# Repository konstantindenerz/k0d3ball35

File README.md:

# k0d3ball35

Read: **kodeball35**.

Designed and built by [Konstantin Denerz](https://konstantin-denerz.com) ·
[project page](https://konstantin-denerz.com/k0d3ball35/)

k0d3ball35 (kodeball35) is a wireless, low profile, 35-key split keyboard with an integrated 19 mm trackball.
Keyball-inspired column stagger and thumb arc, Kailh Choc V1 hot-swap switches, a nice!nano v2
on each half, ZMK firmware, two flat angular PCBs (18 keys left, 17 keys right) and the ball in a
case pocket right beside the thumb keys.

*Concept render, not a photo of a finished build.*

> ## ⚠️ Work in progress — do not build or order parts from this repository
>
> **k0d3ball35 is an unfinished design under active development. Nothing here has been
> manufactured, assembled or tested in hardware.**
>
> - No PCB in this repository has ever been fabricated, populated or electrically verified.
> - No case or cradle part has been printed and fit-checked against real switches, a real
>   trackball or a real battery.
> - Footprints, dimensions, the bill of materials and the firmware are all still changing, and
>   the geometry is revised between revisions without notice.
>
> **Do not send these gerbers to a fab, do not print these STLs, and do not buy components
> against this BOM.** If you do, you will very likely end up with parts that do not fit and
> money you cannot get back. Treat everything here as a design sketch to read, not a build
> guide to follow. Use at your own risk; there is no warranty of any kind.

## Status

| Subsystem | State | Where |
|-----------|-------|-------|
| Design specification | r2.4 (two PCBs, 35 keys, 19 mm ball pocket, battery bay under the controller on both halves) | [spec/01-design-spec.md](spec/01-design-spec.md) |
| Layout generator | r2.4 done, per-half outputs, exact coordinates in [spec/02-layout.md](spec/02-layout.md) | [hardware/layout](hardware/layout) |
| Left PCB (KiCad 10) | r2.4 routed, ERC and DRC clean, gerbers exported; battery bay on the back silkscreen | [hardware/left-pcb](hardware/left-pcb) |
| Right PCB (KiCad 10) | r2.4 routed, ERC and DRC clean, gerbers exported; battery bay on the back silkscreen | [hardware/right-pcb](hardware/right-pcb) |
| Trackball sensor | r2.4: bought PAW3222 module, no board of ours to fabricate; J1 re-ordered to the module's pinout | [spec/08-trackball-module.md](spec/08-trackball-module.md) |
| Trackball cradle | r2.4 pocket mount for 19.05 mm with the module tilted 65 degrees beside the ball, test print pending | [hardware/trackball-cradle](hardware/trackball-cradle) |
| Firmware (ZMK) | r2.4 in progress: 35 keys, one shared pin set | [firmware/zmk-config](firmware/zmk-config) |
| Documentation | build guide, firmware, fabrication, testing written for r2 | [docs](docs) |
| Case | printed tray, controller box cap, PCB guard, pocket cover and hinged lid per half (OpenSCAD); test print pending | [hardware/case](hardware/case), [spec/11-case.md](spec/11-case.md) |
| Tests and CI | pytest suite, workflows ready for GitHub | [tests](tests), [.github/workflows](.github/workflows) |

Open work is tracked as markdown tickets in [issues/](issues/README.md). The r2 change itself is
`hw-two-pcbs-r2`. Before the first PCB order, work through `hw-main-pcb-review-r1`,
`test-fab-gerber-viewer`, `hw-19mm-ball-sourcing` and a cradle test print (see
[spec/09-roadmap.md](spec/09-roadmap.md)).

## Features

- 35 keys: 3 rows x 5 columns per half plus 3 thumb keys on the left and 2 on the right (the ball
  takes the third position), 18 x 17 mm pitch
- Column stagger and thumb arc derived from the Keyball39 geometry, scaled to Choc spacing
- Kailh Choc V1 switches in hot-swap sockets (hot-swap only, like the Keyball)
- 19.05 mm (3/4 inch) POM trackball on the right half, resting on three 2 mm ceramic balls in a
  printed cradle that stands in a case pocket beside the PCB; bought PAW3222 sensor module tilted
  65 degrees beside the ball, connected with a 6-pin flat cable
- Low: keycaps 20.8 mm over the desk, ball top 23.75 mm, 27.3 mm with the transport lid on
- Fully wireless: nice!nano v2 (or SuperMini nRF52840) per half on 2.5 mm low-profile sockets,
  Bluetooth split, one LiPo cell per half (350 mAh LP552035 right, 150 mAh LP402025 left) in a bay under the PCB below the
  controller (the same bay on both halves), the controller's charger, JST-PH connector, slide
  power switch, reset button
- Two separate PCBs with identical controller wiring: no solder jumpers, no mirrored pin maps,
  no empty ball cutout on the left
- Angular outline: 90 degree steps along the column stagger, rectangular controller block, no rounding
- No LEDs, display or encoder on the PCB, to keep the height and the power draw down
- ZMK firmware on a pinned `main` revision with the PAW3222 driver, automatic mouse layer,
  scroll and snipe modes, ZMK Studio
- All geometry comes from one layout file; schematic, PCB, footprints and tests are generated from the same data

## Repository map

```
spec/                 specification, layout, BOM, build guide, firmware, fabrication, testing
docs/                 the published project page (tabs: exploded view, case, trackball, PCBs, keymap, BOM)
hardware/layout/      layout source (yaml), generated points, outline DXFs and previews per half
hardware/left-pcb/    KiCad project of the left PCB (18 keys), gerbers and renders
hardware/right-pcb/   KiCad project of the right PCB (17 keys, FPC connector, pocket notch)
hardware/lib/         project symbol and footprint libraries
hardware/trackball-cradle/  parametric cradle (pocket mount), STL and floor-footprint DXF exports
hardware/case/        parametric printed case per half (tray, cap, guard, lid), STLs and previews
firmware/zmk-config/  ZMK shield, keymap, build matrix
scripts/              generators and checks (schematic, routing, export, tickets)
tests/                pytest suite incl. KiCad ERC/DRC gates
issues/               markdown tickets and the generated index
```

## Documentation

| Document | Content |
|----------|---------|
| [00 Feasibility](spec/00-feasibility.md) | prior art, ball size research, risks, licensing, why this design |
| [01 Design specification](spec/01-design-spec.md) | requirements, pin map, matrix, FPC interface, geometry contract |
| [02 Layout](spec/02-layout.md) | key coordinates per half, stagger derivation, ball pocket |
| [03 Bill of materials](spec/03-bom.md) | parts, quantities per half, sources |
| [04 Build guide](spec/04-build-guide.md) | step by step assembly |
| [05 Firmware](spec/05-firmware.md) | flashing, pairing, tuning, battery |
| [06 Fabrication](spec/06-fabrication.md) | PCB order settings for both boards, gerber checklist |
| [07 Testing](spec/07-testing.md) | automated checks and bench procedure |
| [08 Trackball module](spec/08-trackball-module.md) | sensor module, cable, heights, pocket mount |
| [09 Roadmap](spec/09-roadmap.md) | verification before ordering, case, dongle, sensor variants |
| [10 Lessons from Keyball](spec/10-lessons-from-keyball.md) | holykeebs and Yowkees designs, known weaknesses and our response |
| [11 Printed case](spec/11-case.md) | tray, controller box cap, ball pocket, hinged lid as transport cover and tenting foot |
| [12 Order checklist](spec/12-order-checklist.md) | shop-by-shop parts list, what is ordered, JLCPCB and LCSC lines, printed parts, what waits for hardware |
| [Image prompts](spec/images/PROMPTS.md) | every picture as a generation prompt |

## Project page

The project page, [`docs/index.html`](docs/index.html), is published with GitHub Pages from
`docs/` on `main`. One tab per area: an overview, the interactive 3D exploded view of both halves
(explode slider, half switch, section through the ball, lid modes), the real printed parts of the
case and the trackball cradle, the three boards in 3D and as layer plots and the keymap. The page
shows the files; the markdown keeps the details, and the overview links to it.

The page is static; every file it loads carries a content hash (`?v=`, stamped by `make site`), so a visit never mixes cached files of two versions. It shows the real files: STLs and the KiCad GLBs are fetched from the
repository (raw.githubusercontent.com, branch `main`), nothing is copied into `docs/`. The data the
tabs need (layout, part facts, keymap, board facts) is generated into `docs/data/` by
`docs/build.py`: run `make site` after a change to the layout, the case, the boards, the keymap,
the BOM or the tickets; `tests/test_site.py` fails while the data is stale. `make site-serve`
serves the page with the files of the working tree at http://localhost:8000/docs/, which previews
a branch before it is merged.

## Quick start

```sh
brew install --cask kicad          # KiCad 10.0.7 (copy the app from the DMG if the cask asks for admin rights)
brew install openjdk               # Java for freerouting
brew install --cask openscad@snapshot   # OpenSCAD with the manifold backend, for the case and cradle
uv venv .venv && uv pip install --python .venv/bin/python -e ".[test]"
make freerouting-jar               # downloads freerouting 2.5.0 to build/
make test                          # full test suite
```

## Build the hardware files

Everything under `hardware/left-pcb/` and `hardware/right-pcb/` is generated; edit
`hardware/layout/k0d3ball35.yaml` and `scripts/k0d3/` instead of the KiCad files.

```sh
make layout                                   # points-*.json, outline-*.dxf, previews for both halves
JAVA=/opt/homebrew/opt/openjdk/bin/java \
FREEROUTING_JAR=build/freerouting.jar \
make sch pcb route gerbers                    # both halves: schematic + ERC, PCB, freerouting, DRC, export
scripts/build_board.sh right                  # one half: schematic + ERC, unrouted PCB, freerouting, DRC (retries until clean)
scripts/export.sh right                       # one half: gerbers, drill, zip, STEP, renders, schematic PDF, BOM, position file
make erc drc                                  # the KiCad gates on their own
make -C hardware/trackball-cradle             # cradle STLs, floor DXF, previews, stack.json
make case-data case                           # hardware/case: data.scad from the layout, tray/cap/lid STLs, previews, stack.json (needs OpenSCAD)
```

`HALVES=right make route` limits the looping targets to one half. `scripts/build_board.sh` expects
`kicad-cli` and KiCad's bundled Python at
`/Applications/KiCad/KiCad.app/Contents/MacOS/kicad-cli` and
`/Applications/KiCad/KiCad.app/Contents/Frameworks/Python.framework/Versions/Current/bin/python3`;
override with `KICAD_CLI=` and `KPY=`. Since r2.4 the two halves are the only KiCad projects in
the repository: the trackball sensor is a bought PAW3222 module, so there is nothing to generate
or fabricate for it.

Firmware is built by GitHub Actions from `firmware/zmk-config`; see
[spec/05-firmware.md](spec/05-firmware.md) for local builds and flashing.

```prompt
Top-down studio render of the right half of a low profile split keyboard, white background, soft
shadows. Bare black PCB with an angular, stepped outline, 17 Kailh Choc hot-swap sockets, small
SOD-123 diodes next to each key, two thumb key positions at the lower inner side and the ball
pocket where a third would be, a nice!nano
controller on low profile sockets in a rectangular block at the inner edge, a dashed rectangle
printed on the board under it marking the battery bay on the other face, an octagonal notch in the lower outer edge of the board where a beige
printed cradle holding a white 19 mm ball stands beside the PCB, a tiny flat flex cable running
from the cradle round the cup to a connector on the PCB. Clean, technical, product photography style.
```

## Credits

- [Keyball](https://github.com/Yowkees/keyball) by Yowkees: the column stagger, thumb arc and the
  idea of a trackball at the thumb are the design inspiration. No Keyball files are used.
- [torabo-tsuki-lp](https://github.com/sekigon-gonnoc/torabo-tsuki-lp) by sekigon-gonnoc: reference
  for a low profile trackball with 25 and 19.05 mm POM balls and the PAW3222 module on a flat cable.
- [LiNEA40](https://github.com/keyfreaks/LiNEA40) by keyfreaks: precedent for a 19 mm ball on a PMW3610.
- [roBa](https://github.com/kumamuk-git/roBa) by kumamuk: reference for a ZMK trackball split with
  PMW3610.
- [kiswitch](https://github.com/kiswitch/kiswitch) and [marbastlib](https://github.com/ebastler/marbastlib):
  switch, socket and controller footprints.
- [ZMK](https://zmk.dev) and sekigon-gonnoc's PAW3222 driver (`zmk-driver-paw3222`).

```prompt
Three quarter view close-up of the trackball pocket on the right half: a matte white 19 mm ball
sitting low in a round pocket of a boxy beige 3D printed case, in line with two burnt orange thumb
keycaps to its left, the ball top only a little higher than the keycaps, three tiny ceramic balls just visible
at the rim of the beige cradle, light grey Choc keycaps behind, the angular stepped case edge
visible. Oak desk, soft daylight, macro lens, shallow depth of field.
```

## License

Copyright (c) 2026 Konstantin Denerz.

Firmware, scripts and documentation: [MIT](LICENSE).
Hardware (everything under `hardware/`): [CERN-OHL-P-2.0](LICENSE-HARDWARE).

The `kode` wordmark on the PCB silkscreen, the case and the project page is the author's mark and
is not covered by either licence; a fork keeps the design files and replaces the artwork. See
[NOTICE](NOTICE).

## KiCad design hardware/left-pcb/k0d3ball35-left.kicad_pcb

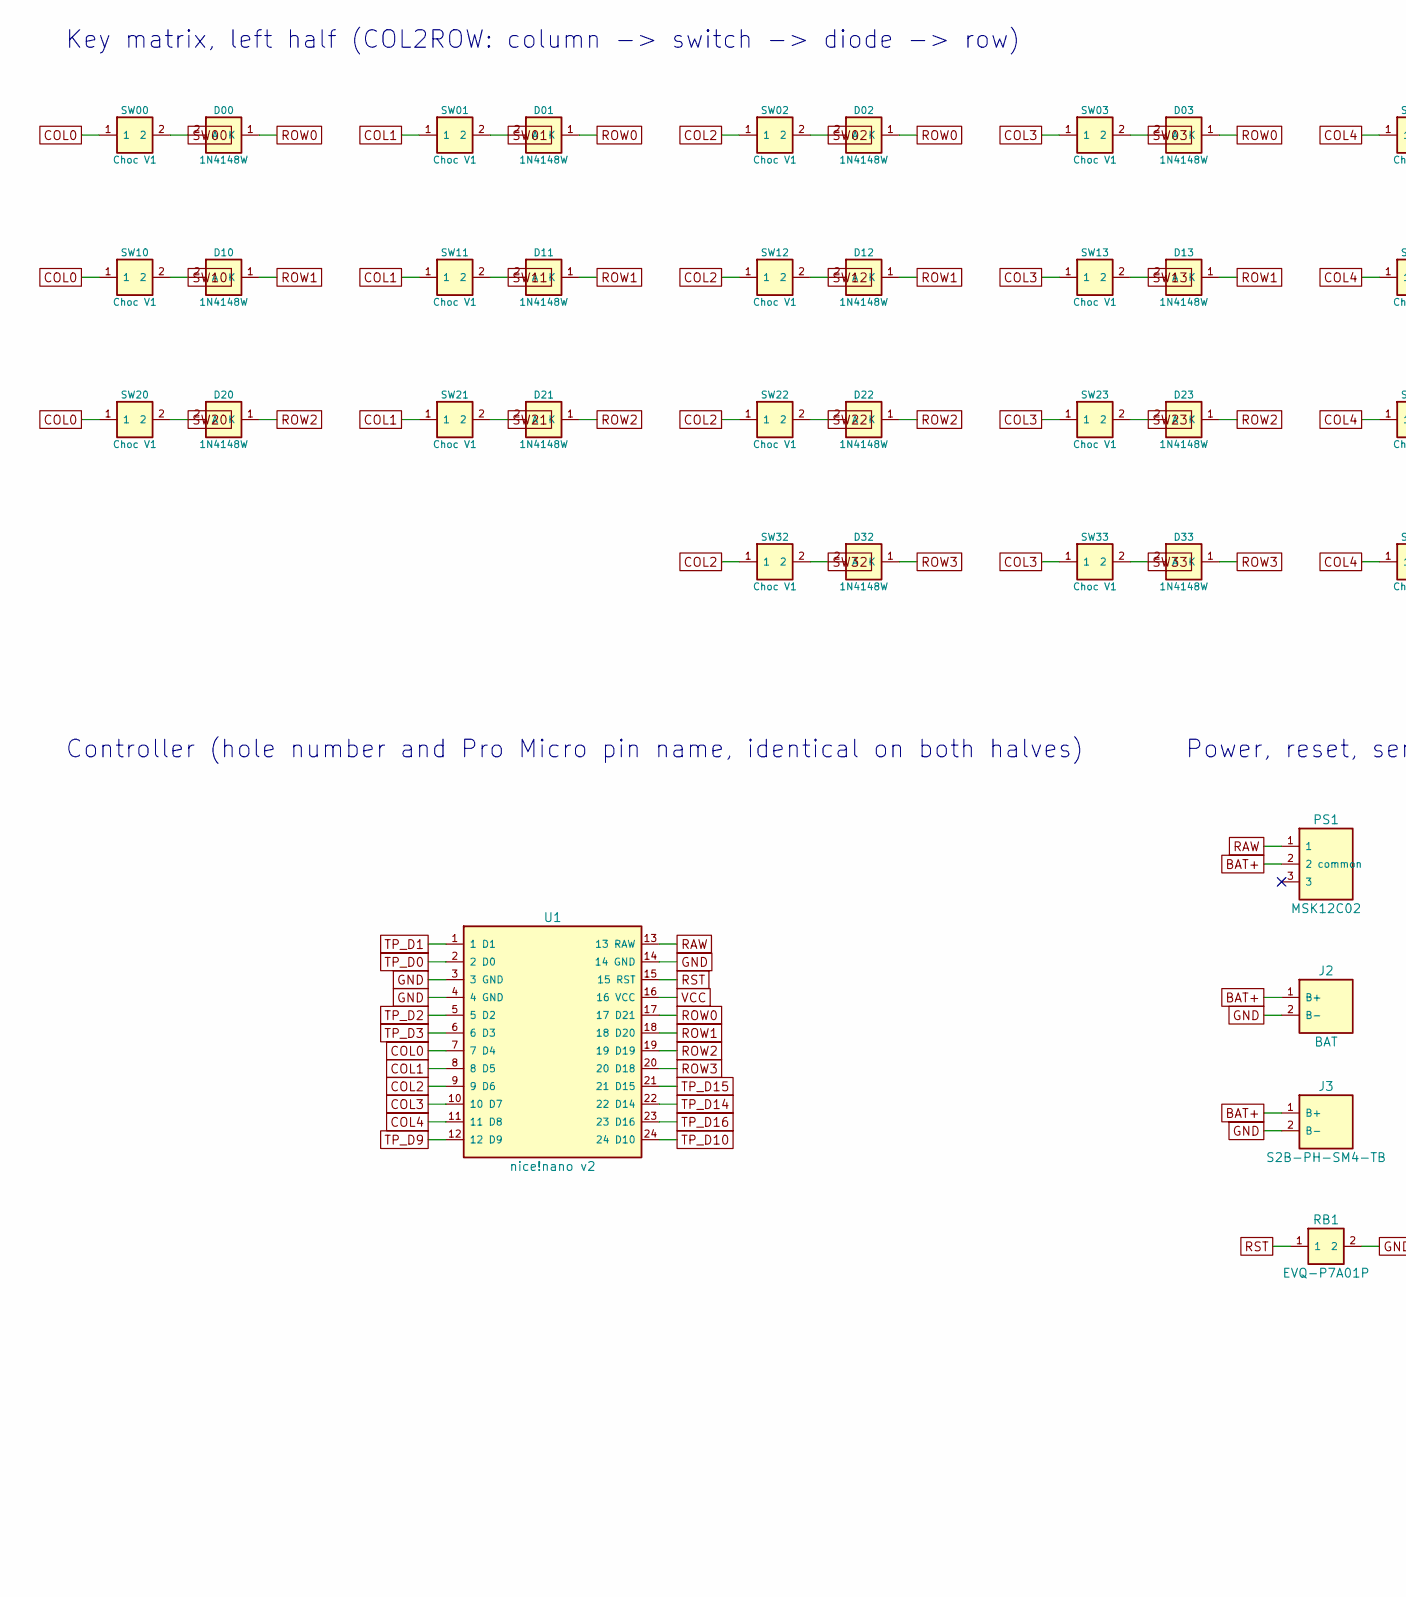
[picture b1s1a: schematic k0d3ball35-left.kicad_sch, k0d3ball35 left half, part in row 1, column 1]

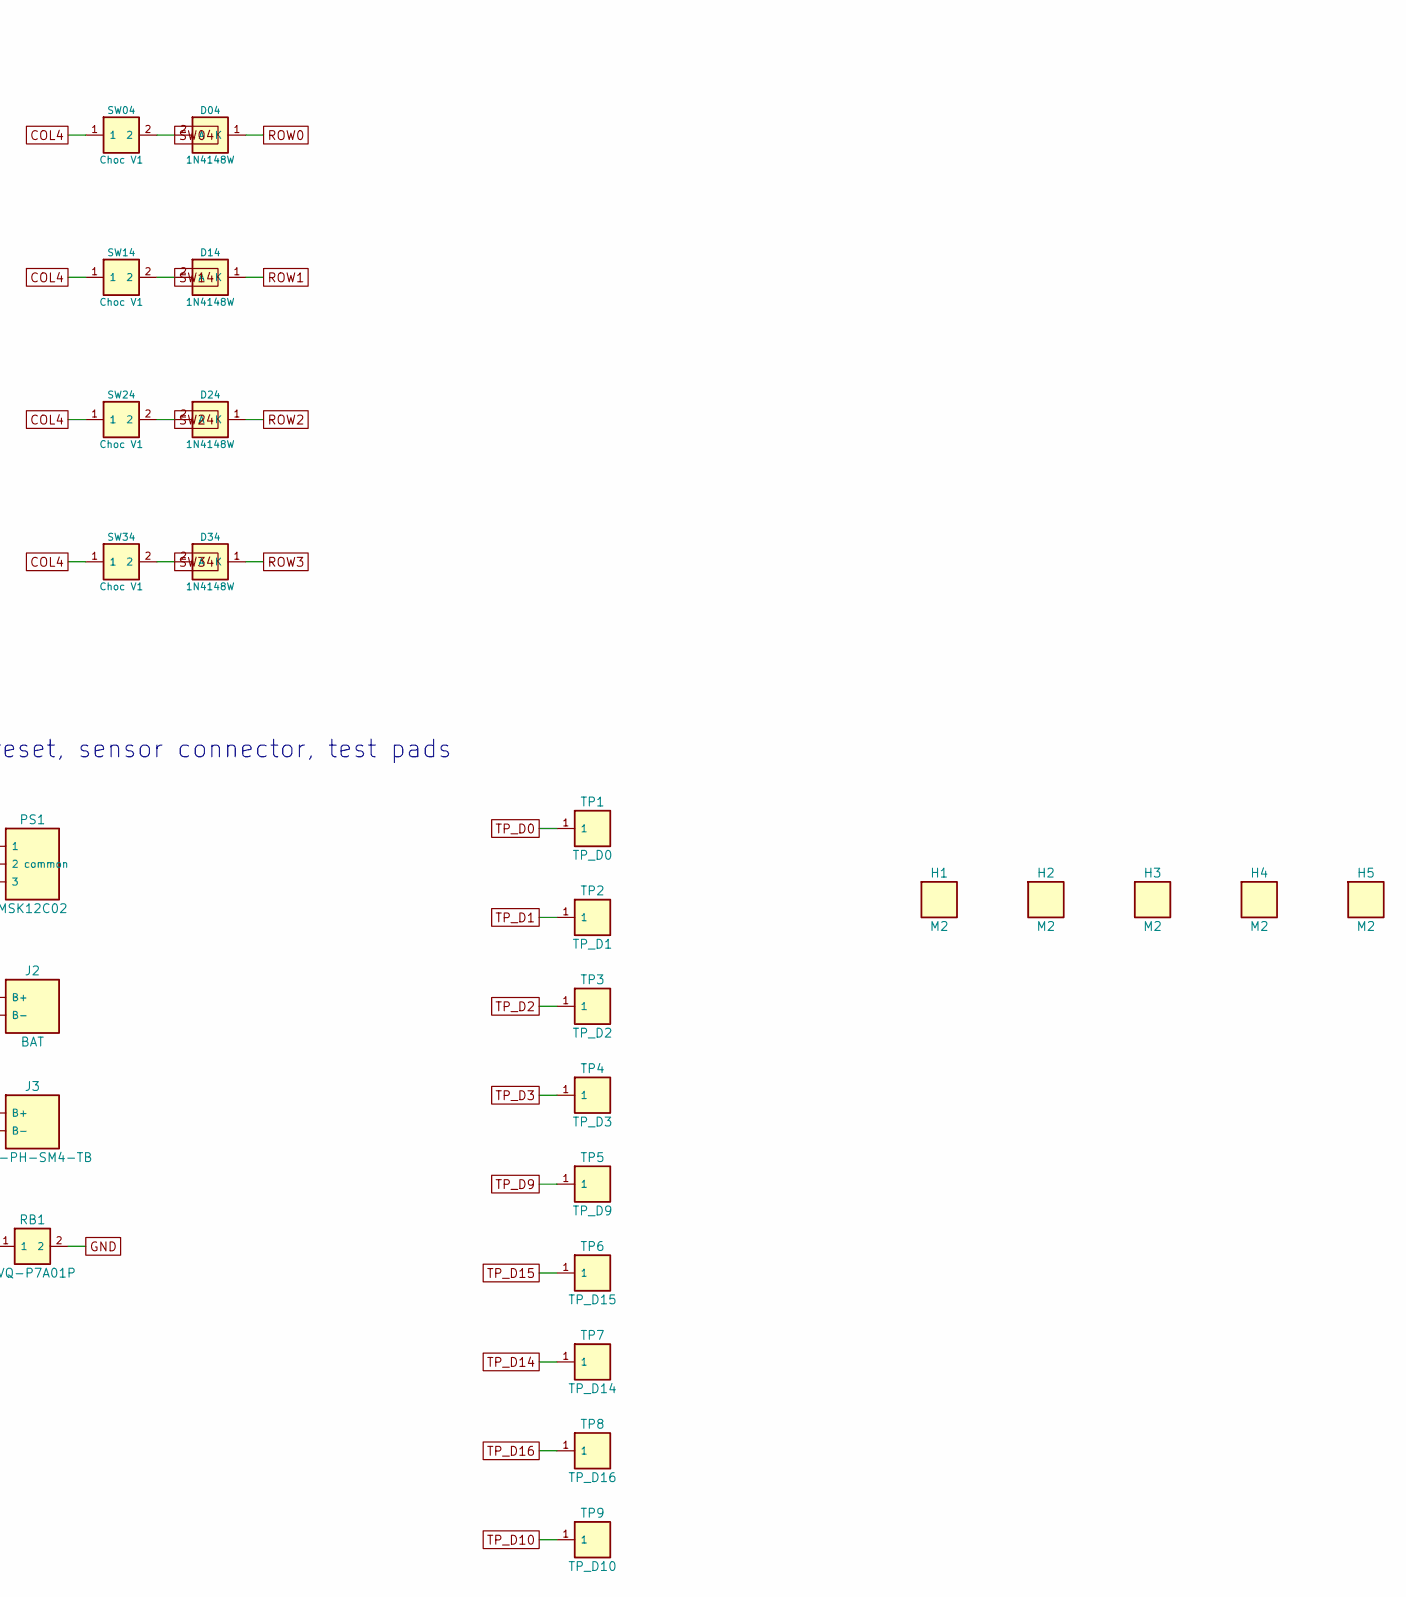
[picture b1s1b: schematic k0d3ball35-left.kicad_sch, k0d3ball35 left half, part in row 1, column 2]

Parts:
D00, D01, D02, D03, D04, D10, D11, D12, D13, D14, D20, D21, D22, D23, D24, D32, D33, D34: 1N4148W; D_SOD-123_reversible
H1, H2, H3, H4, H5: M2; MountingHole_2.2mm
J2: BAT; BatteryPads_2x1.8mm_P2.54mm
J3: S2B-PH-SM4-TB; JST_PH_S2B-PH-SM4-TB_reversible
PS1: MSK12C02; SW_SPDT_MSK12C02_reversible
RB1: EVQ-P7A01P; SW_SPST_EVQP7A_reversible
SW00, SW01, SW02, SW03, SW04, SW10, SW11, SW12, SW13, SW14, SW20, SW21, SW22, SW23, SW24, SW32, SW33, SW34: Choc V1; SW_Choc_V1_HS_reversible
TP1: TP_D0; TestPad_1.5mm
TP2: TP_D1; TestPad_1.5mm
TP3: TP_D2; TestPad_1.5mm
TP4: TP_D3; TestPad_1.5mm
TP5: TP_D9; TestPad_1.5mm
TP6: TP_D15; TestPad_1.5mm
TP7: TP_D14; TestPad_1.5mm
TP8: TP_D16; TestPad_1.5mm
TP9: TP_D10; TestPad_1.5mm
U1: nice!nano v2; nice_nano_v2_THT

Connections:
BAT+: J2.1 (B+), J3.1 (B+), PS1.2 (2 common)
COL0: SW00.1, SW10.1, SW20.1, U1.7 (7 D4)
COL1: SW01.1, SW11.1, SW21.1, U1.8 (8 D5)
COL2: SW02.1, SW12.1, SW22.1, SW32.1, U1.9 (9 D6)
COL3: SW03.1, SW13.1, SW23.1, SW33.1, U1.10 (10 D7)
COL4: SW04.1, SW14.1, SW24.1, SW34.1, U1.11 (11 D8)
GND: J2.2 (B-), J3.2 (B-), RB1.2, U1.3 (3 GND), U1.4 (4 GND), U1.14 (14 GND)
RAW: PS1.1, U1.13 (13 RAW)
ROW0: D00.1 (K), D01.1 (K), D02.1 (K), D03.1 (K), D04.1 (K), U1.17 (17 D21)
ROW1: D10.1 (K), D11.1 (K), D12.1 (K), D13.1 (K), D14.1 (K), U1.18 (18 D20)
ROW2: D20.1 (K), D21.1 (K), D22.1 (K), D23.1 (K), D24.1 (K), U1.19 (19 D19)
ROW3: D32.1 (K), D33.1 (K), D34.1 (K), U1.20 (20 D18)
RST: RB1.1, U1.15 (15 RST)
SW00: D00.2 (A), SW00.2
SW01: D01.2 (A), SW01.2
SW02: D02.2 (A), SW02.2
SW03: D03.2 (A), SW03.2
SW04: D04.2 (A), SW04.2
SW10: D10.2 (A), SW10.2
SW11: D11.2 (A), SW11.2
SW12: D12.2 (A), SW12.2
SW13: D13.2 (A), SW13.2
SW14: D14.2 (A), SW14.2
SW20: D20.2 (A), SW20.2
SW21: D21.2 (A), SW21.2
SW22: D22.2 (A), SW22.2
SW23: D23.2 (A), SW23.2
SW24: D24.2 (A), SW24.2
SW32: D32.2 (A), SW32.2
SW33: D33.2 (A), SW33.2
SW34: D34.2 (A), SW34.2
TP_D0: TP1.1, U1.2 (2 D0)
TP_D1: TP2.1, U1.1 (1 D1)
TP_D2: TP3.1, U1.5 (5 D2)
TP_D3: TP4.1, U1.6 (6 D3)
TP_D9: TP5.1, U1.12 (12 D9)
TP_D10: TP9.1, U1.24 (24 D10)
TP_D14: TP7.1, U1.22 (22 D14)
TP_D15: TP6.1, U1.21 (21 D15)
TP_D16: TP8.1, U1.23 (23 D16)
VCC: U1.16 (16 VCC)

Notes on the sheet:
Key matrix, left half (COL2ROW: column -> switch -> diode -> row)
Controller (hole number and Pro Micro pin name, identical on both halves)
Power, reset, sensor connector, test pads

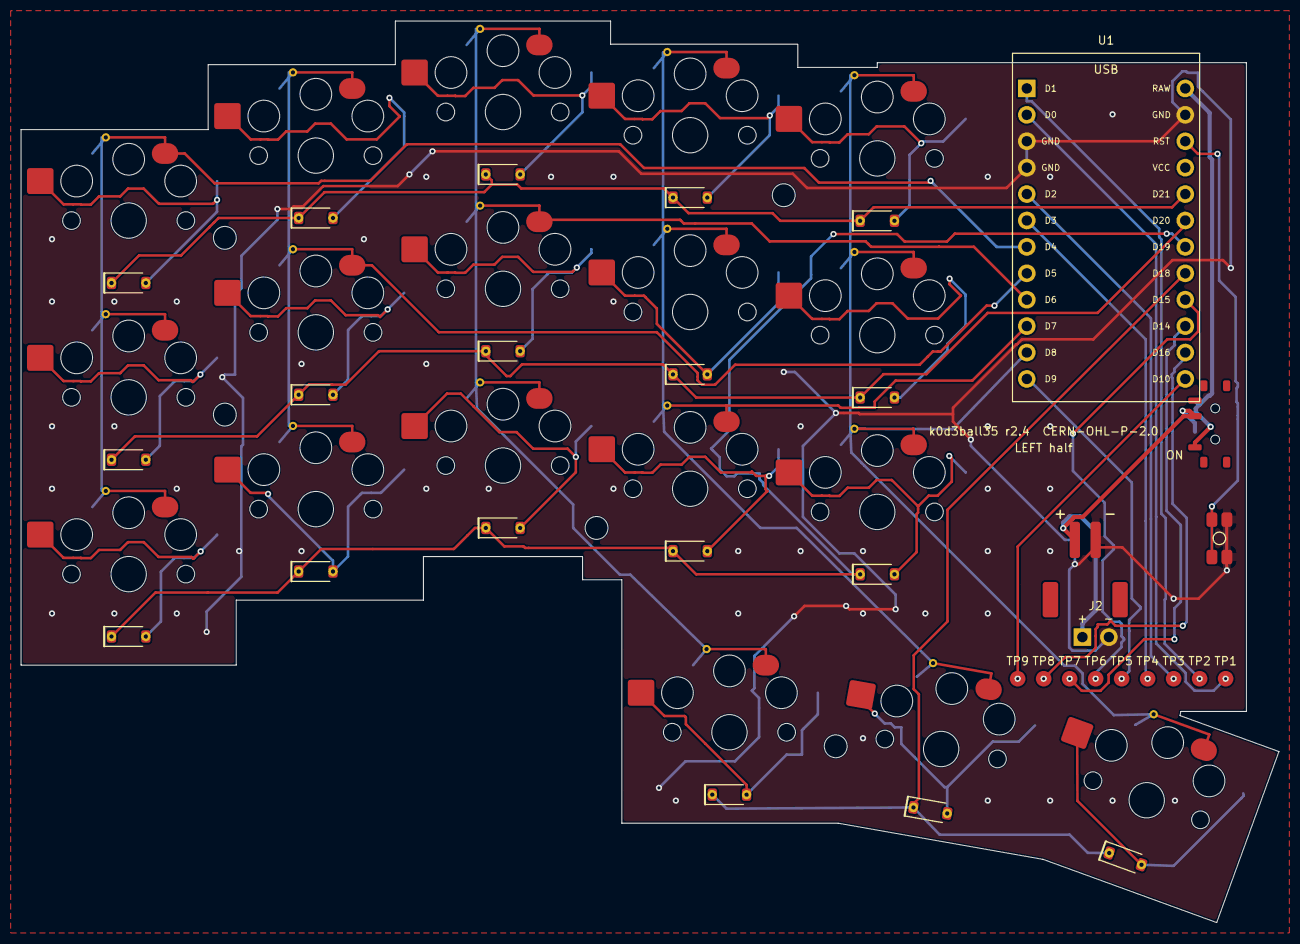
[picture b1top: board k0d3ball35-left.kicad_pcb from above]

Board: 2 copper layers, 121.0 x 86.7 mm, 55 parts (0 on the bottom side), 40 nets.

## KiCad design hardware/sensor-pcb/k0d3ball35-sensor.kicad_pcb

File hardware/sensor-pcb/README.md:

# Sensor board (PMW3610 daughterboard)

26 x 25 mm, two layer, 1.6 mm FR4. Carries the PixArt PMW3610DM-SUDU laser sensor with its
LM18-LSI lens, a 1.8 V regulator and a 6-pin 0.5 mm FPC connector to the main PCB.
Design notes, stack-up and the FFC orientation rule are in `spec/08-trackball-module.md`.

## Files

| Path | Content |
|------|---------|
| `generate.py` | single source of truth: parts, nets, placement; writes schematic, PCB and libraries |
| `export.sh` | ERC/DRC gates, gerbers, drill, pick-and-place, BOM, renders, STEP |
| `k0d3ball35-sensor.kicad_pro/.kicad_sch/.kicad_pcb` | generated KiCad 10 project (committed so it can be opened directly) |
| `gerbers/`, `fab/` | JLCPCB-ready outputs (`fab/*-gerbers.zip`, `*-bom.csv`, `*-cpl-*.csv`) |
| `renders/` | schematic PDF/SVG, PCB renders, STEP model for the cradle design |
| `build/` | scratch (DSN/SES, reports), ignored by git |

## Regenerate

```sh
# Python bundled with KiCad 10 (provides pcbnew); freerouting jar in build/ or $FREEROUTING_JAR
/Applications/KiCad/KiCad.app/Contents/Frameworks/Python.framework/Versions/Current/bin/python3 generate.py all
./export.sh
```

`generate.py all` writes libraries, schematic and an unrouted PCB, autoroutes it with freerouting,
adds the ground pours and re-runs ERC and DRC (with schematic parity) until the result is clean.
`export.sh` refuses to export when ERC or DRC report errors.

## Ordering

JLCPCB: 2 layer, 1.6 mm, any colour, ENIG recommended (flat pads under the 0.5 mm connector),
"remove order number: specify location" not needed. Upload `fab/k0d3ball35-sensor-r1-gerbers.zip`.
For assembly use the BOM and the top-side CPL; the sensor (U1) is a through-hole part on the
bottom side and is soldered by hand together with the lens.

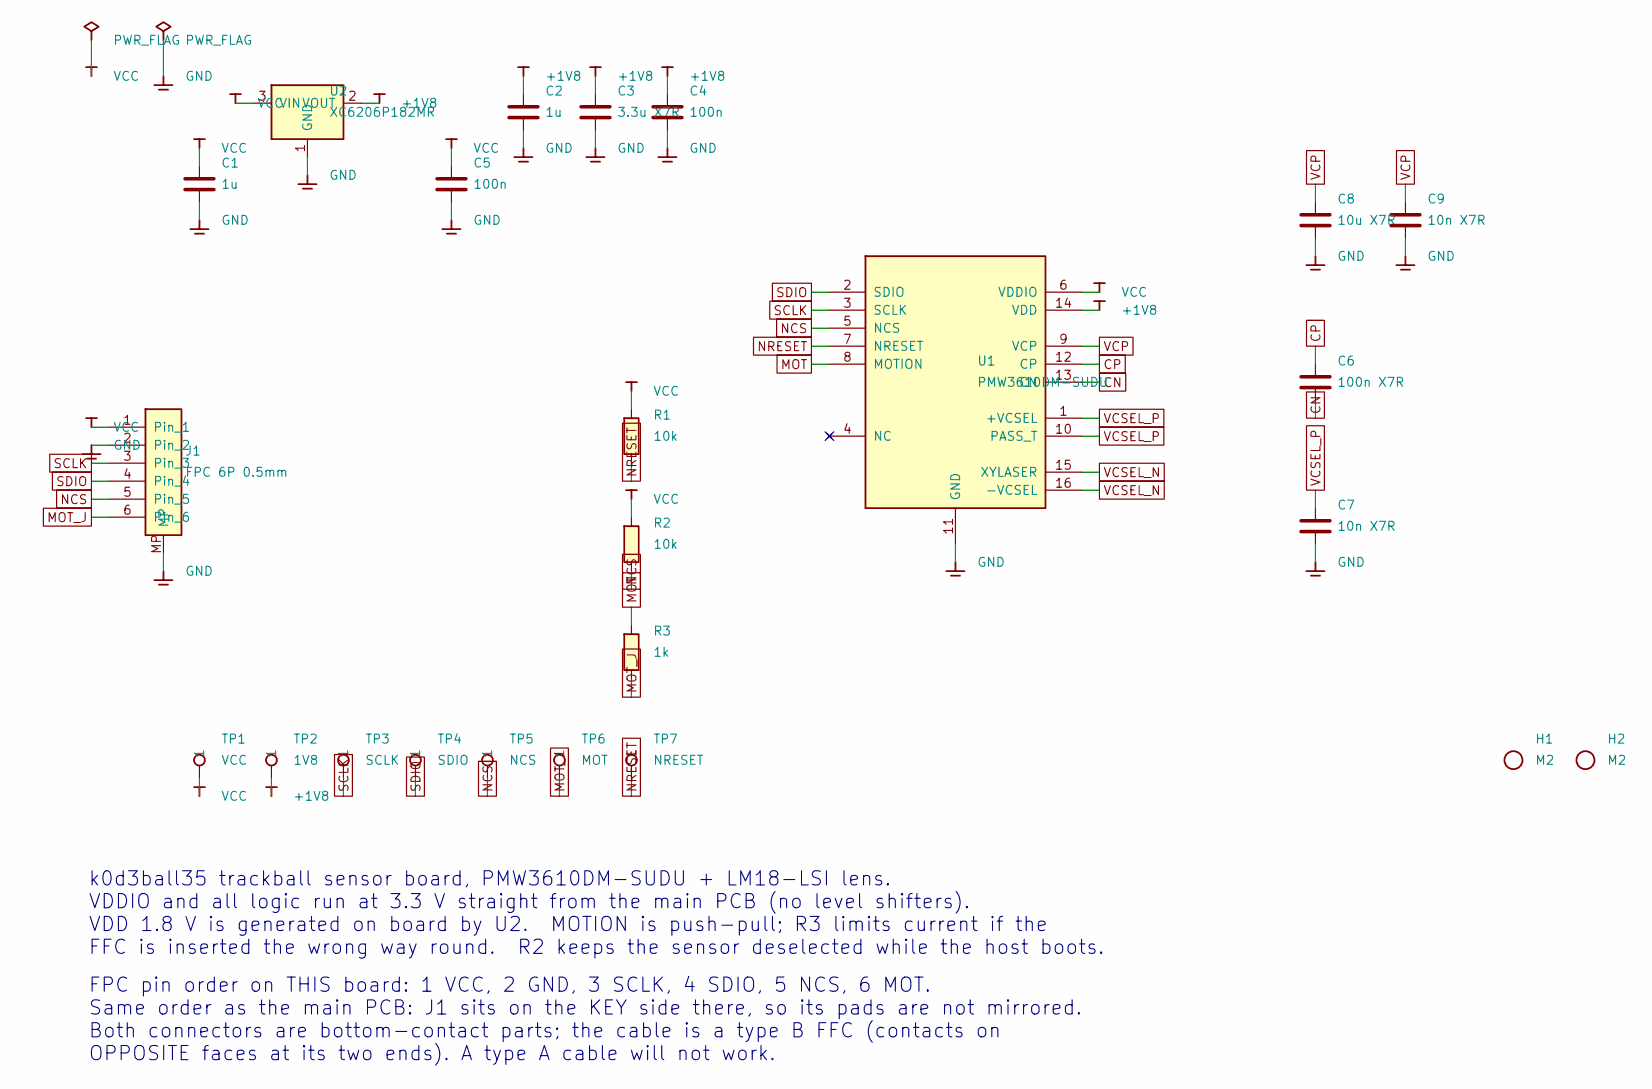
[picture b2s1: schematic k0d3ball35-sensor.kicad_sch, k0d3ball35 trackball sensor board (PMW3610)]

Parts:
C1, C2: 1u; C_0603; LCSC C15849
C3: 3.3u X7R; C_0603; LCSC C1678
C4, C5: 100n; C_0603; LCSC C14663
C6: 100n X7R; C_0603; LCSC C14663
C7, C9: 10n X7R; C_0603; LCSC C57112
C8: 10u X7R; C_0603; LCSC C19702
H1, H2: M2; MountingHole_M2
J1: FPC 6P 0.5mm; FPC_0.5mm_6P_FH12-6S; LCSC C2764370
R1, R2: 10k; R_0603; LCSC C25804
R3: 1k; R_0603; LCSC C21190
TP1: VCC; TestPoint_D1.0mm
TP2: 1V8; TestPoint_D1.0mm
TP3: SCLK; TestPoint_D1.0mm
TP4: SDIO; TestPoint_D1.0mm
TP5: NCS; TestPoint_D1.0mm
TP6: MOT; TestPoint_D1.0mm
TP7: NRESET; TestPoint_D1.0mm
U1: PMW3610DM-SUDU; LCSC C42442560
U2: XC6206P182MR; SOT-23; LCSC C5446

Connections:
+1V8: C2.1, C3.1, C4.1, TP2.1, U1.14 (VDD), U2.2 (VOUT)
CN: C6.2, U1.13 (CN)
CP: C6.1, U1.12 (CP)
GND: C1.2, C2.2, C3.2, C4.2, C5.2, C7.2, C8.2, C9.2, J1.2, J1.MP, U1.11 (GND), U2.1 (GND)
MOT: R3.1, U1.8 (MOTION)
MOT_J: J1.6, R3.2, TP6.1
NCS: J1.5, R2.2, TP5.1, U1.5 (NCS)
NRESET: R1.2, TP7.1, U1.7 (NRESET)
SCLK: J1.3, TP3.1, U1.3 (SCLK)
SDIO: J1.4, TP4.1, U1.2 (SDIO)
VCC: C1.1, C5.1, J1.1, R1.1, R2.1, TP1.1, U1.6 (VDDIO), U2.3 (VIN)
VCP: C8.1, C9.1, U1.9 (VCP)
VCSEL_N: U1.15 (XYLASER), U1.16 (-VCSEL)
VCSEL_P: C7.1, U1.1 (+VCSEL), U1.10 (PASS_T)

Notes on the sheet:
k0d3ball35 trackball sensor board, PMW3610DM-SUDU + LM18-LSI lens. VDDIO and all logic run at 3.3 V straight from the main PCB (no level shifters). VDD 1.8 V is generated on board by U2. MOTION is push-pull; R3 limits current if the FFC is inserted the wrong way round. R2 keeps the sensor deselecte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
FPC pin order on THIS board: 1 VCC, 2 GND, 3 SCLK, 4 SDIO, 5 NCS, 6 MOT. Same order as the main PCB: J1 sits on the KEY side there, so its pads are not mirrored. Both connectors are bottom-contact parts; the cable is a type B FFC (contacts on OPPOSITE faces at its two ends). A type A cable will not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

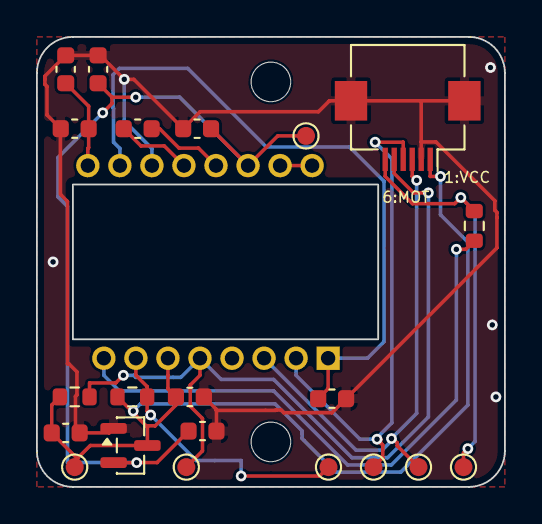
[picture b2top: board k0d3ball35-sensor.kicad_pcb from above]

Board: 2 copper layers, 26.0 x 25.0 mm, 24 parts (1 on the bottom side), 14 nets.

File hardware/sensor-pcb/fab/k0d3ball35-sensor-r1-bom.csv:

"Designator","Value","Footprint","LCSC","Description","Quantity"
"C1,C2","1u","k0d3ball35:C_0603","C15849","1 uF 0603 X5R 10 V, 1.8 V rail,1 uF 0603 X5R 10 V, LDO input","2"
"C3","3.3u X7R","k0d3ball35:C_0603","C1678","3.3 uF 0603 X7R 16 V, 1.8 V rail bulk","1"
"C4,C5","100n","k0d3ball35:C_0603","C14663","100 nF 0603 X7R, VDD decoupling,100 nF 0603 X7R, VDDIO decoupling","2"
"C6","100n X7R","k0d3ball35:C_0603","C14663","100 nF 0603 X7R 16 V, charge pump","1"
"C7,C9","10n X7R","k0d3ball35:C_0603","C57112","10 nF 0603 X7R 16 V, VCP,10 nF 0603 X7R 16 V, VCSEL supply","2"
"C8","10u X7R","k0d3ball35:C_0603","C19702","10 uF 0603 X7R 16 V, VCP","1"
"J1","FPC 6P 0.5mm","k0d3ball35:FPC_0.5mm_6P_FH12-6S","C2764370","0.5 mm 6-pos FPC connector, bottom contact, FH12-6S-0.5SH or clone (type B cable)","1"
"R1,R2","10k","k0d3ball35:R_0603","C25804","10 k 0603, NCS pull-up,10 k 0603, NRESET pull-up","2"
"R3","1k","k0d3ball35:R_0603","C21190","1 k 0603, MOTION series protection","1"
"U1","PMW3610DM-SUDU","k0d3ball35:PMW3610DM-SUDU","C42442560","PixArt low power laser mouse sensor, 16-pin molded DIP, LM18-LSI lens","1"
"U2","XC6206P182MR","k0d3ball35:SOT-23","C5446","Torex 1.8 V 200 mA LDO, SOT-23","1"

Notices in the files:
hardware/left-pcb/k0d3ball35-left.kicad_pcb:
k0d3ball35 r2.4  CERN-OHL-P-2.0
hardware/left-pcb/k0d3ball35-left.kicad_sch:
Licensed under CERN-OHL-P-2.0
